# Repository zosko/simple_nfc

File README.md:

# SimpleNFC

This hardware emulate ISO 14443-3 NFC tags

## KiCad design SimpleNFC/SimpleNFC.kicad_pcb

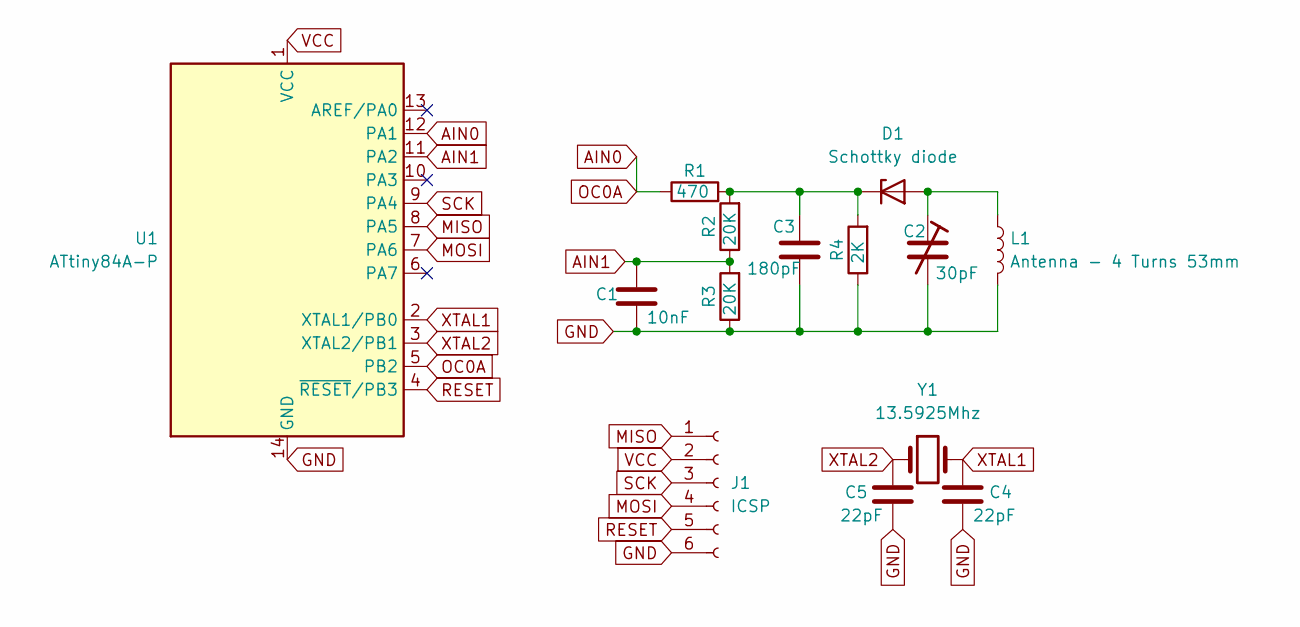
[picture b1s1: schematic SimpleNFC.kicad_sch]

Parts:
C1: 10nF; C_Disc_D4.3mm_W1.9mm_P5.00mm
C2: 30pF; C_Disc_D4.3mm_W1.9mm_P5.00mm
C3: 180pF; C_Disc_D4.3mm_W1.9mm_P5.00mm
C4, C5: 22pF; C_Disc_D4.3mm_W1.9mm_P5.00mm
D1: Schottky diode; D_A-405_P7.62mm_Horizontal
J1: ICSP; PinHeader_2x03_P2.54mm_Vertical
L1: Antenna - 4 Turns 53mm; L_Axial_L7.0mm_D3.3mm_P10.16mm_Horizontal_Fastron_MICC
R1: 470; R_Axial_DIN0207_L6.3mm_D2.5mm_P7.62mm_Horizontal
R2, R3: 20K; R_Axial_DIN0207_L6.3mm_D2.5mm_P7.62mm_Horizontal
R4: 2K; R_Axial_DIN0207_L6.3mm_D2.5mm_P7.62mm_Horizontal
U1: ATtiny84A-P; DIP-14_W7.62mm
Y1: 13.5925Mhz; Crystal_HC49-U_Vertical

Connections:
AIN0: R1.1, U1.5 (PB2), U1.12 (PA1)
AIN1: C1.1, R2.1, R3.2, U1.11 (PA2)
GND: C1.2, C2.2, C3.2, C4.2, C5.2, J1.6, L1.2, R3.1, R4.1, U1.14 (GND)
MISO: J1.1, U1.8 (PA5)
MOSI: J1.4, U1.7 (PA6)
unnamed: C2.1, D1.2 (A), L1.1
unnamed: C3.1, D1.1 (K), R1.2, R2.2, R4.2
RESET: J1.5, U1.4 (~RESET/PB3)
SCK: J1.3, U1.9 (PA4)
VCC: J1.2, U1.1 (VCC)
XTAL1: C4.1, U1.2 (XTAL1/PB0), Y1.2
XTAL2: C5.1, U1.3 (XTAL2/PB1), Y1.1

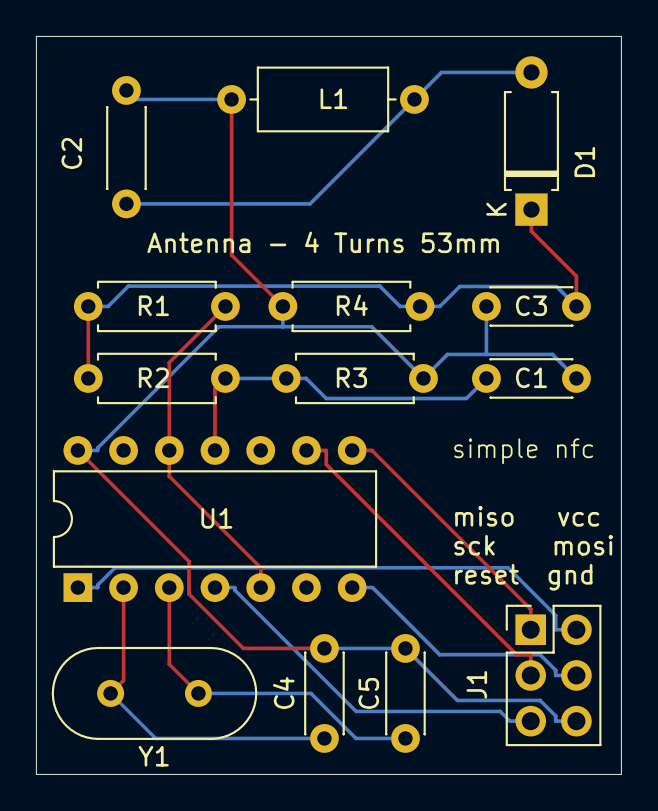
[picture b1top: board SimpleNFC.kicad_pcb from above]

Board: 2 copper layers, 32.5 x 41.0 mm, 14 parts (0 on the bottom side), 12 nets.

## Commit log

2025-02-03 fix design, add firmware, build script
